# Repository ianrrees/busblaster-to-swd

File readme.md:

JTAG adapter: 20-pin ARM to Cortex SWD w/ 10-pin 0.05" or 6-pin Tag Connect
===

Gerber files have been confirmed to work for basic SWD programming via the Tag Connect header.

Available from my DirtyPCBs shop: http://dirtypcbs.com/store/designer/details/9294/3545/busblaster-to-swd-gerbers-zip

The repo started out as a "universal adapter", which became somewhat intractable.
However, in that attempt I accumulated a few JTAG pinout links:

  * http://www.jtagtest.com/pinouts/ - Several pinouts
  * http://www.tincantools.com/assets/ARM20OnCE14_Rev-A_%20schematic.pdf - 20-pin TI
  * http://processors.wiki.ti.com/index.php/JTAG_Connectors - TI docs
  * http://www.analog.com/media/en/dsp-documentation/evaluation-kit-manuals/ICE_emu_1000_2000_rev_manual.pdf - Blackfin pinout
  * http://www.atmel.com/webdoc/atmelice/atmelice.using_ocd_physical_jtag.html - Atmel ICE
  * http://www.tag-connect.com/Materials/ARM20-CTX.pdf - Tag Connect's SWD adapter

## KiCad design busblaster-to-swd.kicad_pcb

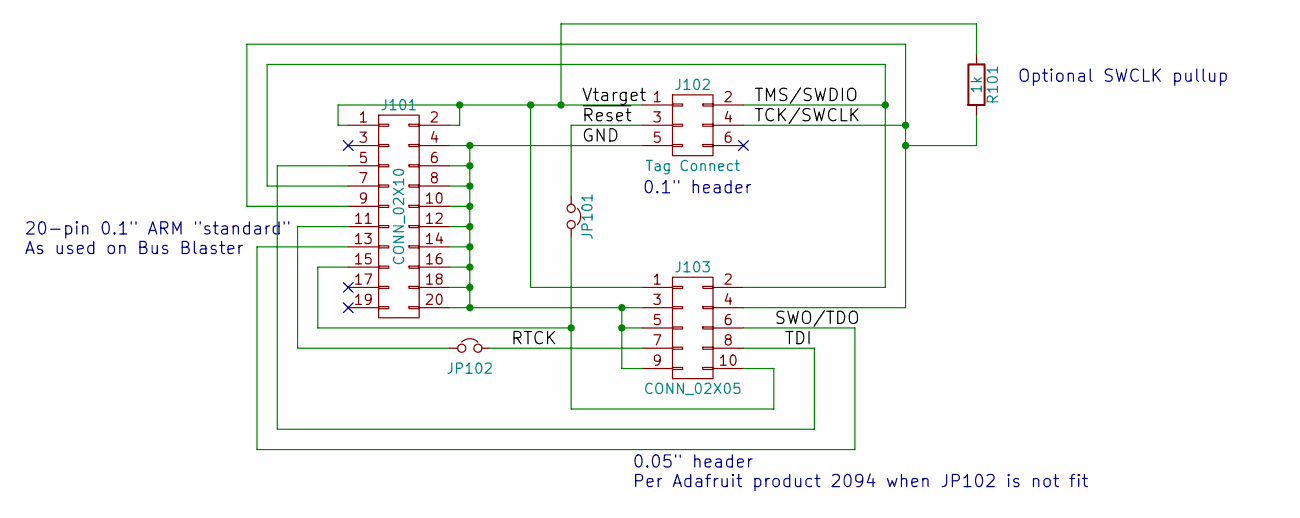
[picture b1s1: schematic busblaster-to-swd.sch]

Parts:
J101: CONN_02X10; Pin_Header_Straight_2x10_Pitch2.54mm
J102: Tag Connect; Pin_Header_Straight_2x03_Pitch2.54mm
J103: CONN_02X05; Pin_Header_Straight_2x05_Pitch1.27mm
JP101, JP102: Jumper_NC_Small; R_0603_HandSoldering
R101: 1k; R_0603_HandSoldering

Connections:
/GND: J101.4, J101.6, J101.8, J101.10, J101.12, J101.14, J101.16, J101.18, J101.20, J102.5, J103.3, J103.5, J103.9
/RTCK: J103.7, JP102.2
/SWO/TDO: J101.13, J103.6
/TCK/SWCLK: J101.9, J102.4, J103.4, R101.2
/TDI: J101.5, J103.8
/TMS/SWDIO: J101.7, J102.2, J103.2
/Vtarget: J101.1, J101.2, J102.1, J103.1, R101.1
/~Reset: J102.3, JP101.1
unnamed: J101.11, JP102.1
unnamed: J101.15, J103.10, JP101.2

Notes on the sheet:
20-pin 0.1" ARM "standard" As used on Bus Blaster
0.1" header
0.05" header Per Adafruit product 2094 when JP102 is not fit
Optional SWCLK pullup

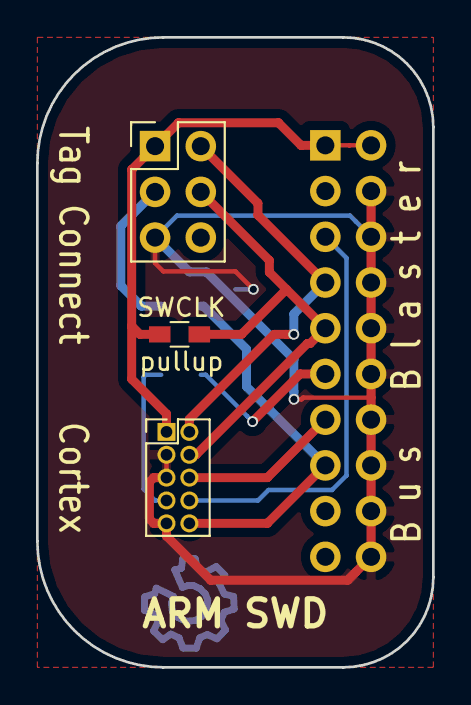
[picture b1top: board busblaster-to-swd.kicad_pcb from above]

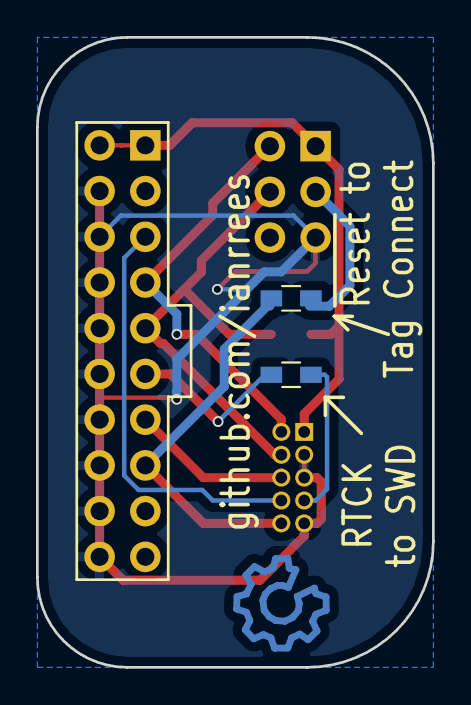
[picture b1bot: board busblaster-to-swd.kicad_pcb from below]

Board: 2 copper layers, 22.0 x 35.0 mm, 6 parts (2 on the bottom side), 10 nets.

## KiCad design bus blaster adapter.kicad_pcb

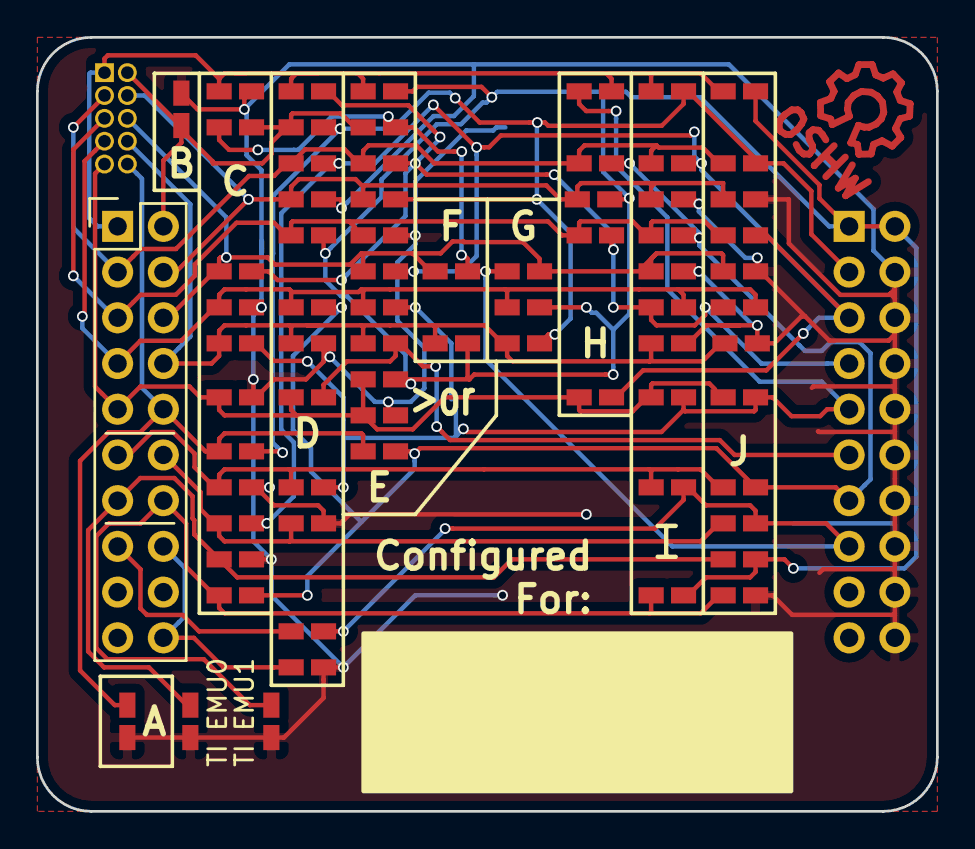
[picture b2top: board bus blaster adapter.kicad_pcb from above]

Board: 2 copper layers, 50.0 x 43.0 mm, 73 parts (0 on the bottom side), 25 nets.

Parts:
JP101, JP102, JP103, JP104, JP105, JP106, JP107, JP108, JP109, JP110, JP111, JP112, JP113, JP114, JP115, JP116, JP117, JP118, JP119, JP120, JP121, JP122, JP123, JP124, JP125, JP126, JP127, JP128, JP129, JP130, JP131, JP132, JP133, JP134, JP135, JP136, JP137, JP138, JP139, JP140, JP141, JP142, JP143, JP144, JP145, JP146, JP147, JP148, JP149, JP150, JP151, JP152, JP153, JP154, JP155, JP156, JP157, JP158, JP159, JP160, JP161, JP162, JP163, JP164, JP165, JP166, JP167, JP168, JP169, JP170: Jumper_NO_Small; 0603_jumper
P101, P102: CONN_02X10; Pin_Header_Straight_2x10
P103: CONN_02X05; 10pin_1.27pitch

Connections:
/RTCK: JP111.1, JP155.1, P101.11
/TCK: JP107.1, JP115.1, JP116.1, JP119.1, JP136.1, JP153.1, P101.9
/TDI: JP114.1, JP127.1, JP128.1, JP131.1, JP148.1, JP162.1, P101.5
/TDO: JP109.1, JP118.1, JP126.1, JP130.1, JP161.1, JP165.1, P101.13
/TMS: JP121.1, JP122.1, JP125.1, JP129.1, JP134.1, JP147.1, P101.7
/TRST: JP132.1, JP137.1, JP140.1, JP143.1, JP157.1, JP160.1, P101.3
/TSRST: JP103.1, JP108.1, JP139.1, JP141.1, JP149.1, JP150.1, JP163.1, P101.15
/VTREF: JP105.1, JP112.1, JP120.1, JP123.1, JP135.1, JP138.1, JP144.1, JP156.1, JP166.1, P101.1, P101.2
GND: JP101.1, JP102.1, JP104.1, JP106.1, JP110.1, JP113.1, JP117.1, JP124.1, JP133.1, JP142.1, JP145.1, JP146.1, JP151.1, JP152.1, JP154.1, JP158.1, JP159.1, JP164.1, JP167.1, JP168.1, JP169.2, JP170.2, P101.4, P101.6, P101.8, P101.10, P101.12, P101.14, P101.16, P101.18, P101.20
unnamed: JP101.2, JP104.2, JP105.2, P102.13
unnamed: JP102.2, JP165.2, JP166.2, JP167.2, P102.14
unnamed: JP103.2, P102.15
unnamed: JP106.2, JP107.2, JP108.2, JP109.2, P102.11
unnamed: JP110.2, JP111.2, JP112.2, JP113.2, JP114.2, JP115.2, JP116.2, P102.9, P103.9
unnamed: JP117.2, JP118.2, JP119.2, JP120.2, JP121.2, JP122.2, P102.7, P103.7
unnamed: JP123.2, JP124.2, JP125.2, JP126.2, JP127.2, P102.5, P103.5
unnamed: JP128.2, JP129.2, JP130.2, JP131.2, JP132.2, P102.3, P103.3
unnamed: JP133.2, JP134.2, JP135.2, JP136.2, JP137.2, JP138.2, P102.1, P103.1
unnamed: JP139.2, JP140.2, JP141.2, JP169.1, P102.2, P103.2
unnamed: JP142.2, JP143.2, JP144.2, JP145.2, JP146.2, P102.4, P103.4
unnamed: JP147.2, JP148.2, JP149.2, JP150.2, JP151.2, JP152.2, P102.6, P103.6
unnamed: JP153.2, JP154.2, JP155.2, JP156.2, JP157.2, JP158.2, JP159.2, P102.8, P103.8
unnamed: JP160.2, JP161.2, JP170.1, P102.10, P103.10
unnamed: JP162.2, JP163.2, JP164.2, P102.12
unnamed: JP168.2, P102.16, P102.20

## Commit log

2016-06-20 Initial commit.
2016-06-21 Changed half-done MSP430 to 10-pin Tag Connect
2016-06-21 Added Blackfin
2016-06-21 Added link to Atmel ICE pinout
2016-06-22 Tidy up, added VREF jumper to AVR.
2016-06-26 Initial stab at a PCB layout
2016-07-18 Layout work, could probably use double checking...
2016-07-18 Copper pours!
2016-07-19 Tidy up, as much as one can call it that...
2017-04-16 Abort attempt at universal adapter
2017-04-16 Quick schematic + layout
2017-04-16 Update license and readme
2017-04-16 Update 20-pin TI link
2017-04-30 Add SWCLK pullup resistor footprint
2017-05-03 Updated layout and included gerbers as ordered
2017-05-27 Connect SWO to Tag-Connect, move SWCLK pullup
2017-05-27 Update readme.md
    Add link to dirtypcbs
2017-05-27 Add pdf of schematic
